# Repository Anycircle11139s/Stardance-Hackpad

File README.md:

# Hack Club Stardance Hackpad

A sleek hackpad made for the Hack Club Stardance YSWS.

By: Darsh Shah ([@Anycircle11139s](https://github.com/Anycircle11139s)) or @NotALarp on slack

<br>

## Overview

I created a custom macropad with 12 keys, an OLED screen, and a rotary encoder. I built it because I wanted to get into Stardance and see how it works, and a hackpad is the perfect way to do that. I designed a custom, sleek case to fit around the PCB, and learned about different types of fillets, like tangent (G1) and curvature (G2). Building this taught me a lot about product design.

## Features

- OLED display
- 12 Cherry MX switches
- Rotary encoder
- Xiao RP2040 microcontroller
- Custom 3D printable case

## Build Steps

1. Order all the parts and 3D print the case.
2. Solder all the parts onto the PCB.
3. Place the PCB inside the case and screw on the lid.
4. Flash the firmware and enjoy!

## Firmware

- Framework: [KMK](https://github.com/KMKfw/kmk_firmware) (CircuitPython)
- Notes: Simple to flash. The OLED display shows "Hackpad", each key acts as a number key (1-12), and the rotary encoder controls volume.

Firmware files and pin mapping are in the [`firmware/`](./firmware) folder.

## Hardware

KiCad schematic, PCB layout, and Gerbers are in the [`hardware/`](./hardware) folder. 3D-printable case files are in the [`enclosure/`](./enclosure) folder. Renders and schematic/PCB screenshots are in [`images/`](./images).

## Bill of Materials

A CSV version is also available at [`BOM.csv`](./BOM.csv).

| Part | Qty | Cost Each | Notes |
|---|---|---|---|
| 0.91" OLED Display | 1 | $0.00 | From Stardance hackpad kit |
| 1N4148 diodes | 12 | $0.00 | From Stardance hackpad kit |
| Cherry MX switches | 12 | $0.00 | From Stardance hackpad kit |
| Rotary encoder | 1 | $0.00 | From Stardance hackpad kit |
| Keycaps | 12 | $0.00 | From Stardance hackpad kit |
| Xiao RP2040 microcontroller | 1 | $0.00 | From Stardance hackpad kit |
| 3D Printed Enclosure | 1 | $0.00 | Printed by Printing Legion |
| M3 Screws | 4 | $0.00 | From Stardance hackpad kit |
|PCB | 1 | $5.50 | From JLCPCB |

Total estimated cost: $5.50

## License

This project is licensed under the MIT License — see [`LICENSE`](./LICENSE) for details.

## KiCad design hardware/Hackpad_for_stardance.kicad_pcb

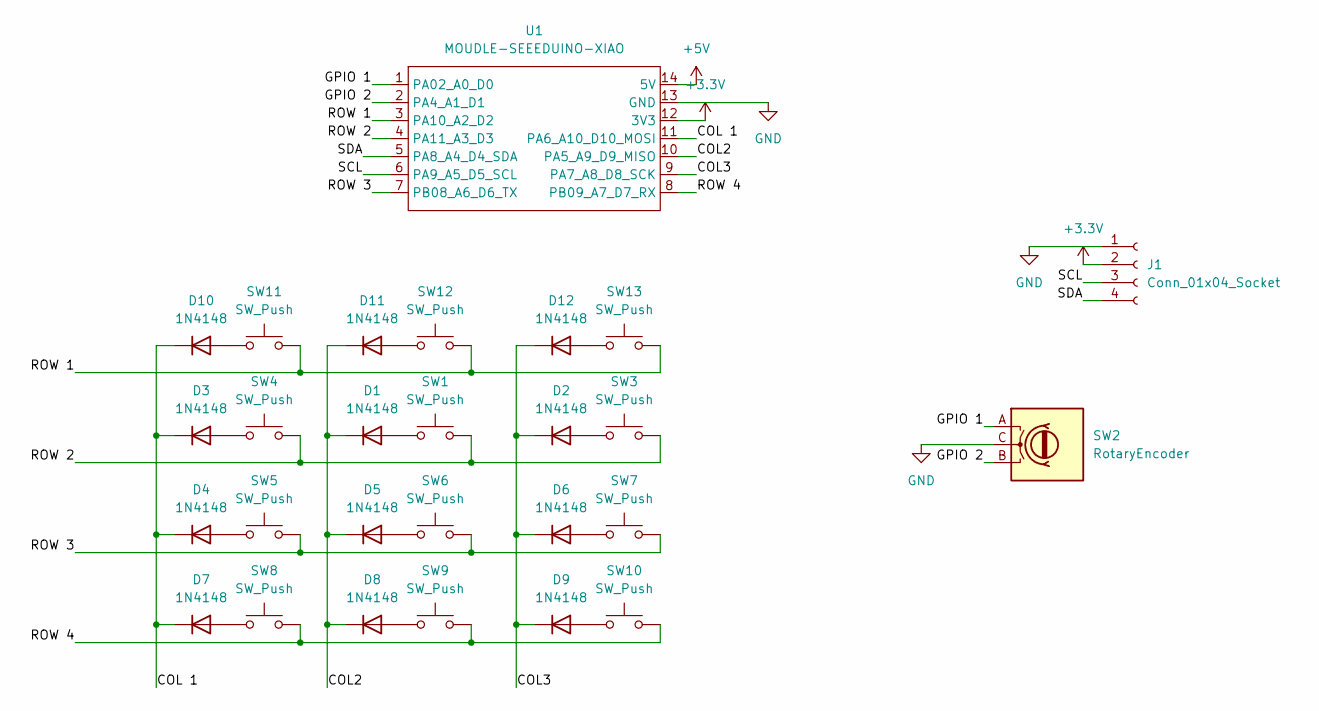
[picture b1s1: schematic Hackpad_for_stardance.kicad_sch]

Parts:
D1, D2, D3, D4, D5, D6, D7, D8, D9, D10, D11, D12: 1N4148; D_DO-35_SOD27_P7.62mm_Horizontal
J1: Conn_01x04_Socket; SSD1306-0.91-OLED-4pin-128x32
SW1, SW3, SW4, SW5, SW6, SW7, SW8, SW9, SW10, SW11, SW12, SW13: SW_Push; SW_Cherry_MX_1.00u_PCB
SW2: RotaryEncoder; RotaryEncoder_Alps_EC11E-Switch_Vertical_H20mm
U1: MOUDLE-SEEEDUINO-XIAO; XIAO RP2040 DIP

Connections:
+3.3V: J1.2, U1.12 (3V3)
+5V: U1.14 (5V)
/COL2: D1.1 (K), D5.1 (K), D8.1 (K), D11.1 (K), U1.10 (PA5_A9_D9_MISO)
/COL3: D2.1 (K), D6.1 (K), D9.1 (K), D12.1 (K), U1.9 (PA7_A8_D8_SCK)
/COL 1: D3.1 (K), D4.1 (K), D7.1 (K), D10.1 (K), U1.11 (PA6_A10_D10_MOSI)
/GPIO 1: SW2.A, U1.1 (PA02_A0_D0)
/GPIO 2: SW2.B, U1.2 (PA4_A1_D1)
/ROW 1: SW11.2, SW12.2, SW13.2, U1.3 (PA10_A2_D2)
/ROW 2: SW1.2, SW3.2, SW4.2, U1.4 (PA11_A3_D3)
/ROW 3: SW5.2, SW6.2, SW7.2, U1.7 (PB08_A6_D6_TX)
/ROW 4: SW8.2, SW9.2, SW10.2, U1.8 (PB09_A7_D7_RX)
/SCL: J1.3, U1.6 (PA9_A5_D5_SCL)
/SDA: J1.4, U1.5 (PA8_A4_D4_SDA)
GND: J1.1, SW2.C, U1.13 (GND)
unnamed: D1.2 (A), SW1.1
unnamed: D2.2 (A), SW3.1
unnamed: D3.2 (A), SW4.1
unnamed: D4.2 (A), SW5.1
unnamed: D5.2 (A), SW6.1
unnamed: D6.2 (A), SW7.1
unnamed: D7.2 (A), SW8.1
unnamed: D8.2 (A), SW9.1
unnamed: D9.2 (A), SW10.1
unnamed: D10.2 (A), SW11.1
unnamed: D11.2 (A), SW12.1
unnamed: D12.2 (A), SW13.1

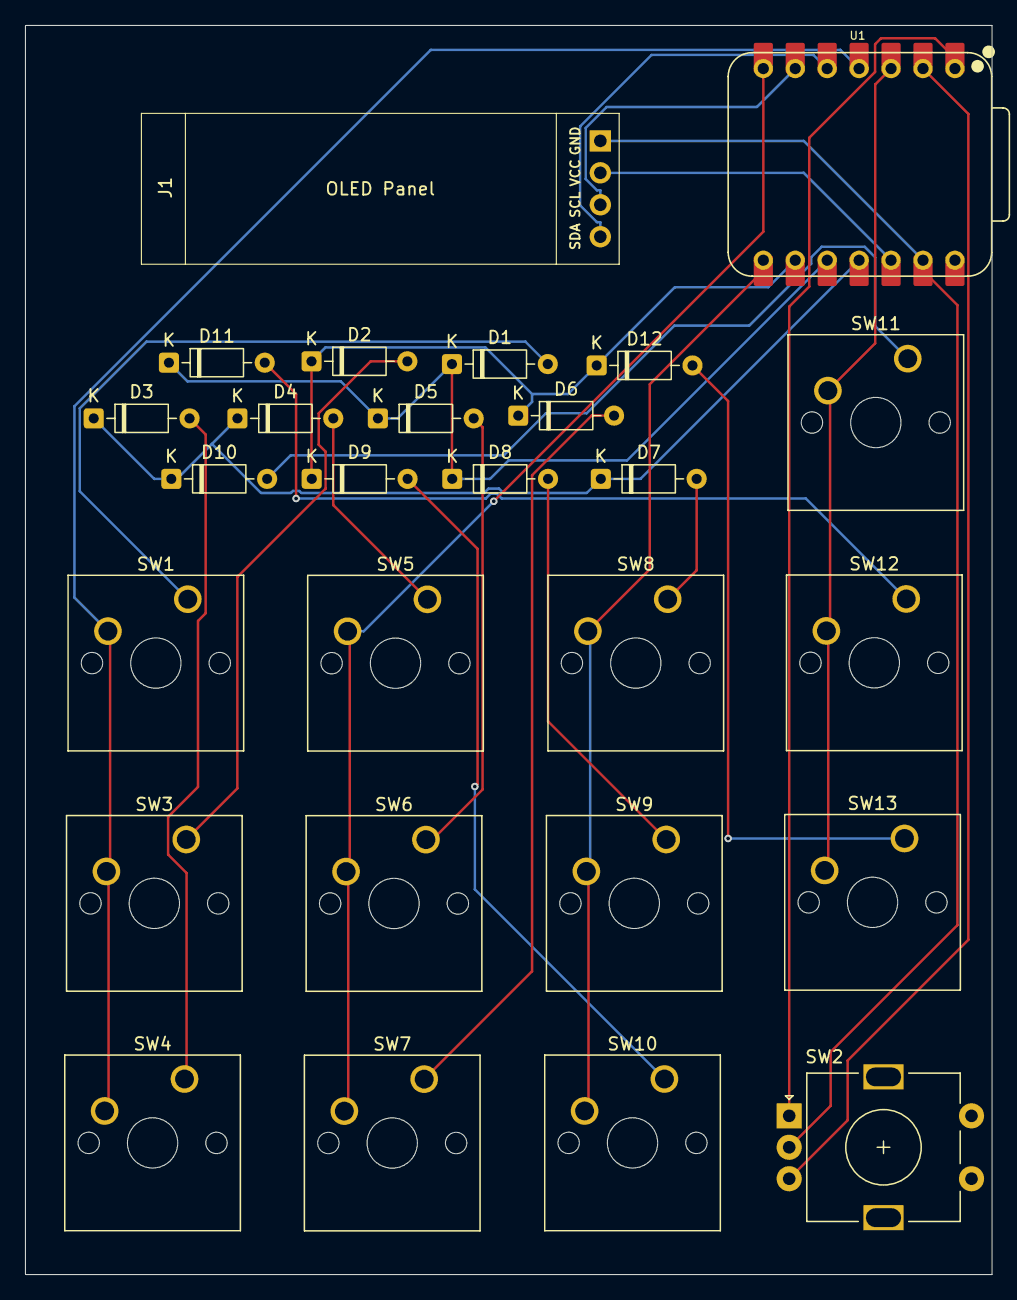
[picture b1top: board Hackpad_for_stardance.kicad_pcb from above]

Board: 2 copper layers, 76.9 x 99.3 mm, 27 parts (0 on the bottom side), 25 nets.
